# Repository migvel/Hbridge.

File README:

======
README
======

Notes:
- Implemented and tested.
- Eagle files.
- Check the DRC check rules and polygon properties depending on the implementation method.

TODO:
- Don´t use external power for the activation of the gates of the MOSFET.

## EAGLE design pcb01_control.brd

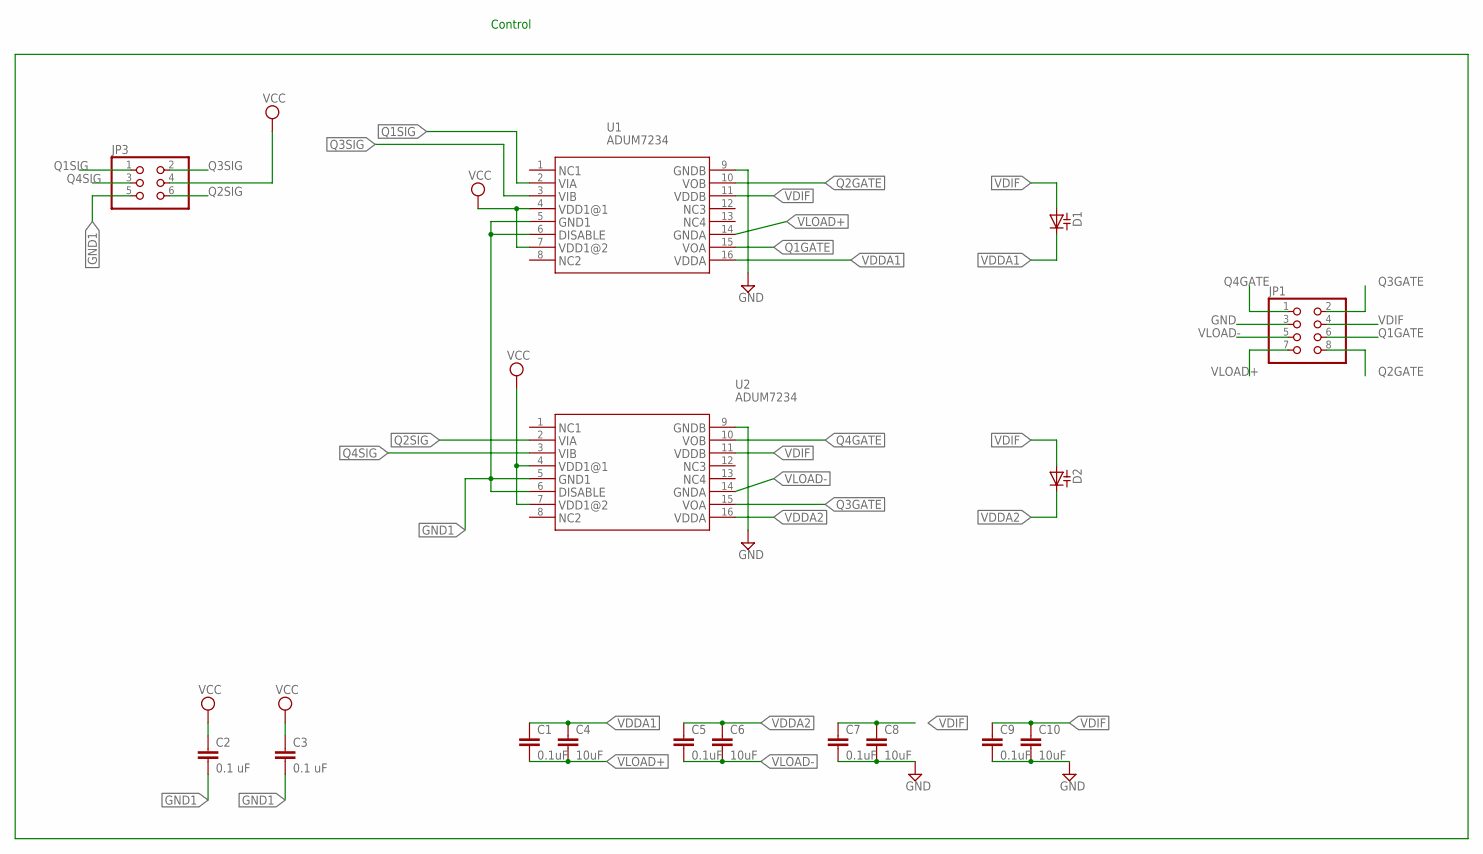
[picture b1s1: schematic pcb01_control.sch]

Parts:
C1, C5, C7, C9: 0.1uF; C0805
C2, C3: 0.1 uF; C0805
C4, C6, C8, C10: 10uF; C0805
D1, D2: DIODE_CAPACITANCE-SOD523; SOD523
JP1: PINHD-2X4; 2X04
JP3: PINHD-2X3; 2X03
U1, U2: ADUM7234; 16_SOIC

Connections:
GND: C7.2, C8.2, C9.2, C10.2, JP1.3, U1.9, U2.9
GND1: C2.2, C3.2, JP3.5, U1.5, U1.6, U2.5, U2.6
Q1GATE: JP1.6, U1.15
Q1SIG: JP3.1, U1.2
Q2GATE: JP1.8, U1.10
Q2SIG: JP3.6, U2.2
Q3GATE: JP1.2, U2.15
Q3SIG: JP3.2, U1.3
Q4GATE: JP1.1, U2.10
Q4SIG: JP3.3, U2.3
VCC: C2.1, C3.1, JP3.4, U1.4, U1.7, U2.4, U2.7
VDDA1: C1.1, C4.1, D1.C, U1.16
VDDA2: C5.1, C6.1, D2.C, U2.16
VDIF: C7.1, C8.1, C9.1, C10.1, D1.A, D2.A, JP1.4, U1.11, U2.11
VLOAD+: C1.2, C4.2, JP1.7, U1.14
VLOAD-: C5.2, C6.2, JP1.5, U2.14

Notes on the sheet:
Control

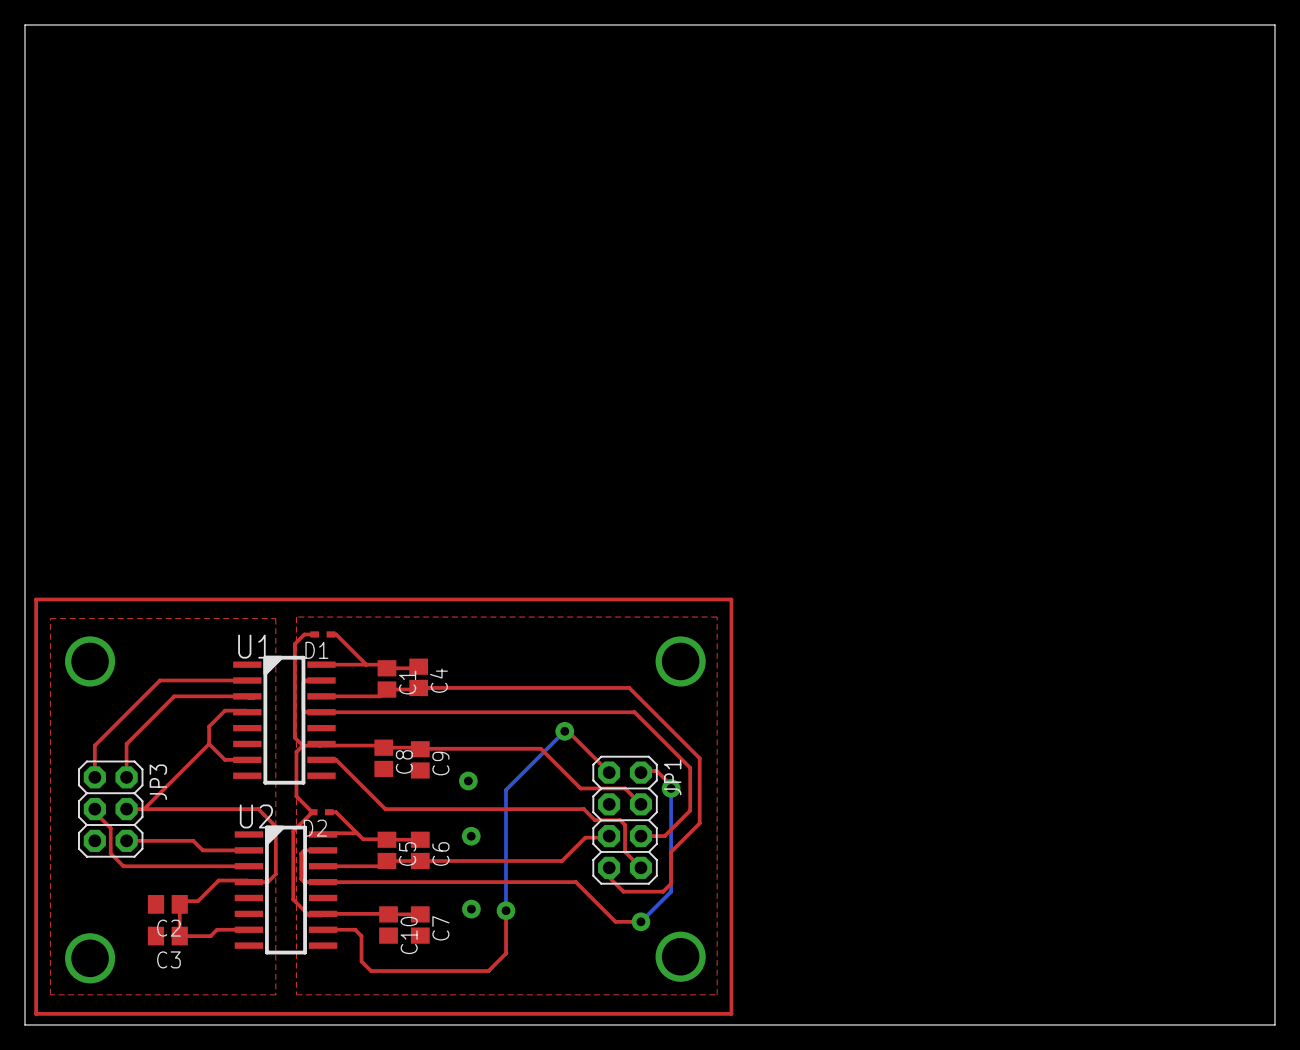
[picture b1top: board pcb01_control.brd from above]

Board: 2 copper layers, 100.0 x 80.0 mm, 16 parts (0 on the bottom side), 16 nets.

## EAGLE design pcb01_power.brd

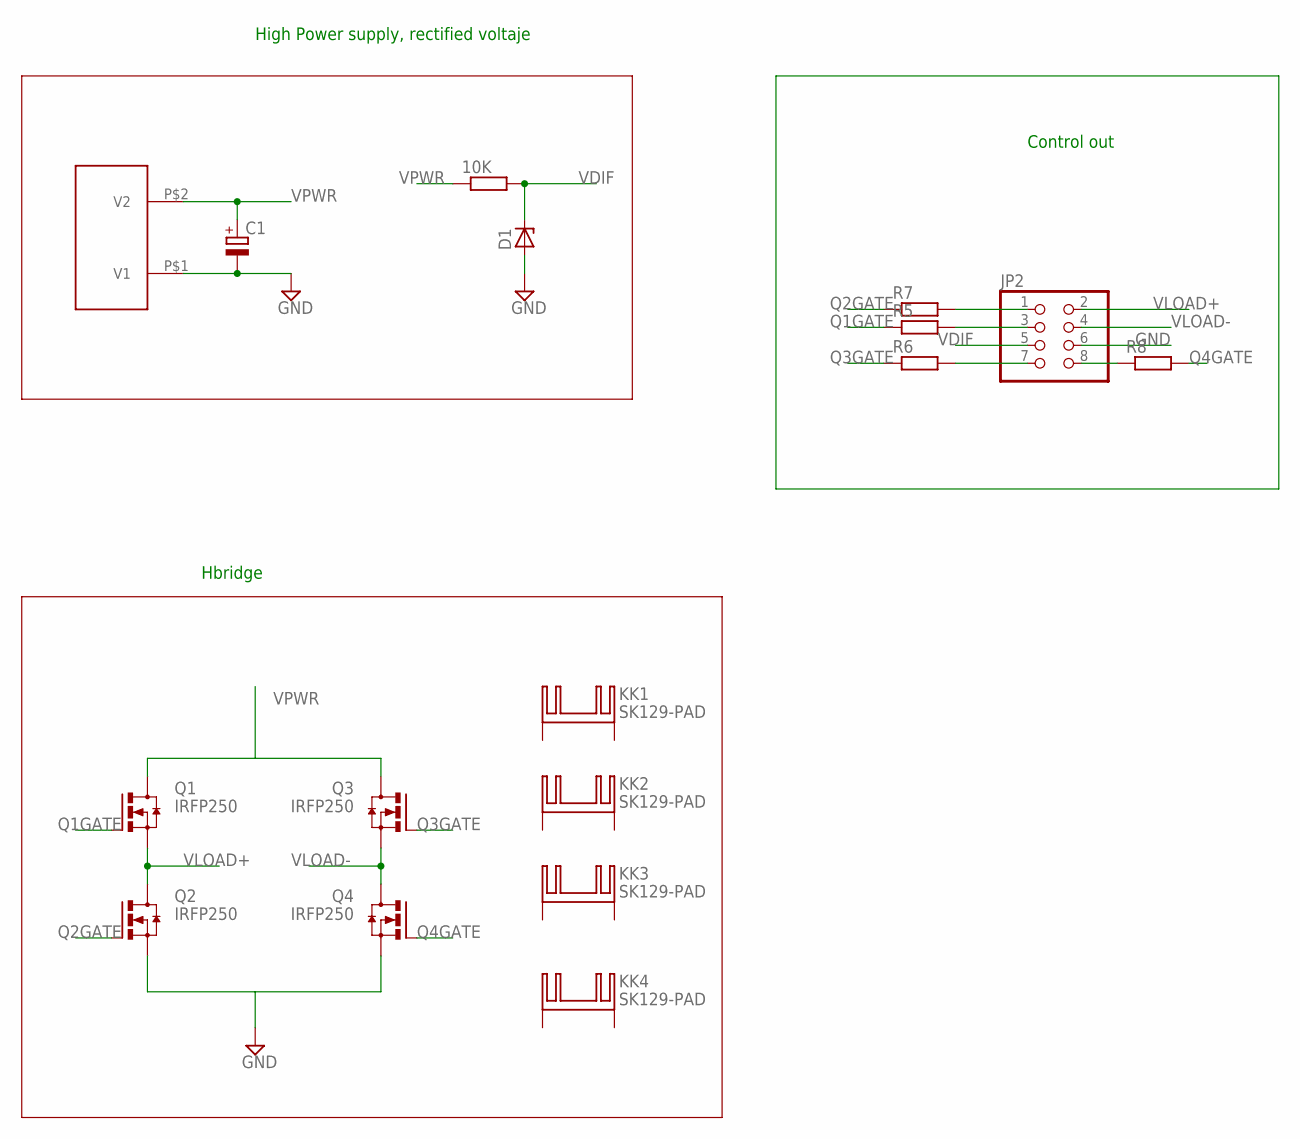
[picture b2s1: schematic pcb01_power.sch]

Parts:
10K: R-EU_V234/12; V234/12
C1: CPOL-EUE7.5-16; E7,5-16
D1: ZENER-DIODEDO35Z10; DO35Z10
JP2: PINHD-2X4; 2X04
KK1, KK2, KK3, KK4: SK129-PAD; SK129
Q1, Q2, Q3, Q4: IRFP250; TO-247AD-V
R5, R6, R7, R8: R-EU_0207/12; 0207/12
U$1: BIGPLUG

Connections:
GND: C1.-, D1.A, JP2.6, Q2.S, Q4.S, U$1.P$1 (V1)
unnamed: JP2.3, R5.2
unnamed: JP2.7, R6.2
unnamed: JP2.1, R7.2
unnamed: JP2.8, R8.1
Q1GATE: Q1.G, R5.1
Q2GATE: Q2.G, R7.1
Q3GATE: Q3.G, R6.1
Q4GATE: Q4.G, R8.2
VDIF: 10K.2, D1.C, JP2.5
VLOAD+: JP2.2, Q1.S, Q2.D
VLOAD-: JP2.4, Q3.S, Q4.D
VPWR: 10K.1, C1.+, Q1.D, Q3.D, U$1.P$2 (V2)

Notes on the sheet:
High Power supply, rectified voltaje
Hbridge
Control out

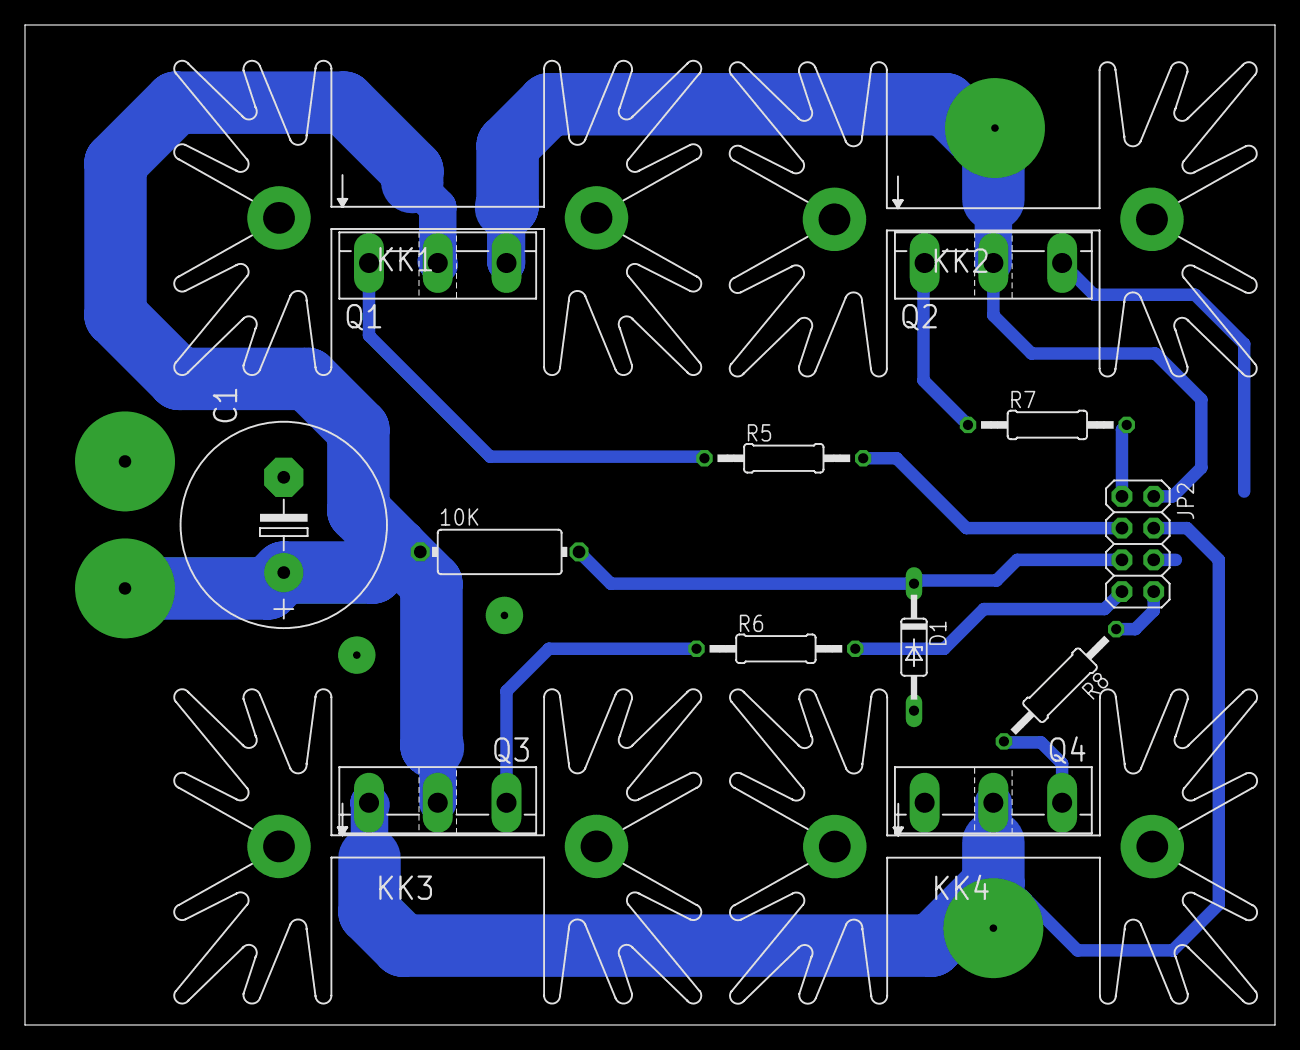
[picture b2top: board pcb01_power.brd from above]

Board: 2 copper layers, 100.0 x 80.0 mm, 17 parts (0 on the bottom side), 13 nets.

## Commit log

2011-09-27 1st commit
2011-09-29 Edited README via GitHub
2013-10-11 new boards update
2013-10-11 deleted old files
